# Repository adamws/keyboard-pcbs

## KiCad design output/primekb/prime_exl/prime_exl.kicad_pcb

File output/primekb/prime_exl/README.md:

## primekb/prime_exl

[layout](prime_exl-kle.json) - [PCB](prime_exl.kicad_pcb)

{:loading="lazy"}

[Open in keyboard-layout-editor](http://www.keyboard-layout-editor.com/##@@_x:0.25&y:0.46&c=#aaaaaa;&=4,0&=5,0&=4,1&=5,1&=4,2&=5,2;&@_x:0.25;&=3,0&=6,0&_c=#cccccc;&=3,1&=6,1&=3,2&_c=#aaaaaa;&=6,2;&@_x:0.25;&=2,0&=7,0&_c=#cccccc;&=2,1&=7,1&=2,2&_c=#aaaaaa;&=7,2;&@_x:0.25;&=1,0&=8,0&_c=#cccccc;&=1,1&=8,1&=1,2&_c=#aaaaaa;&=8,2;&@_x:0.25;&=0,0&=9,0&=0,1&_c=#cccccc;&=9,1&=0,2&_c=#aaaaaa;&=9,2;&@_rx:6.25&x:0.85&y:0.46&c=#777777;&=4,3&_c=#cccccc;&=5,3&_x:8.95;&=4,8&_c=#aaaaaa&w:2;&=5,8;&@_x:0.71&y:0.01&w:1.26;&=3,3&_x:-0.01&c=#cccccc;&=6,3&_x:9.23;&=3,8&_c=#777777&w:1.75;&=6,8;&@_x:0.56&y:0.01&c=#aaaaaa&w:1.75;&=2,3&_c=#cccccc;&=7,3&_x:8.52;&=7,7&=2,8&_c=#aaaaaa&w:1.25;&=7,8;&@_x:0.67&y:0.01&w:1.25;&=1,3&_w:1.25;&=8,3&_x:8.8&w:1.5;&=8,7&_w:1.5;&=1,8;&@_r:8&ry:1&x:3.0&y:-1&c=#cccccc;&=4,4&=5,4&=4,5&=5,5;&@_x:3.25;&=3,4&=6,4&=3,5&=6,5;&@_x:3.75;&=2,4&=7,4&=2,5&=7,5;&@_x:3.75&c=#aaaaaa;&=1,4&=8,4&_w:2;&=1,5;&@_r:-8&x:7.5&y:-1.9&c=#cccccc;&=4,6&=5,6&=4,7&=5,7;&@_x:7.75;&=3,6&=6,6&=3,7&=6,7;&@_x:7.25;&=8,5&=2,6&=7,6&=2,7;&@_x:7.25&c=#aaaaaa&w:2;&=1,6&=8,6&=1,7)

{:loading="lazy"}

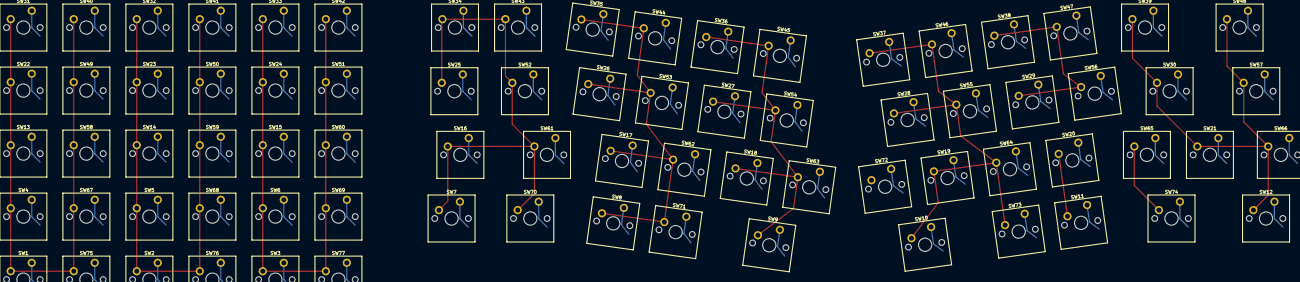
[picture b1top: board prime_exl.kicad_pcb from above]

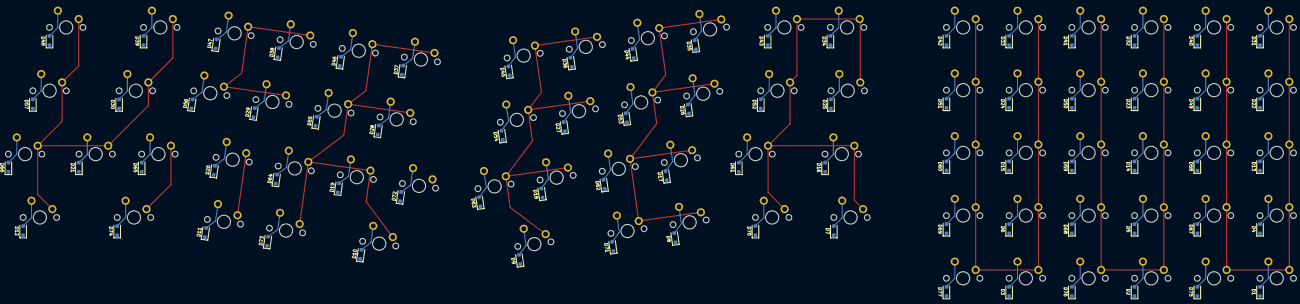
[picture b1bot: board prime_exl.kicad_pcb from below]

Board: 2 copper layers, 154 parts (77 on the bottom side), 96 nets.

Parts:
D1, D2, D3, D4, D5, D6, D7, D8, D9, D10, D11, D12, D13, D14, D15, D16, D17, D18, D19, D20, D21, D22, D23, D24, D25, D26, D27, D28, D29, D30, D31, D32, D33, D34, D35, D36, D37, D38, D39, D40, D41, D42, D43, D44, D45, D46, D47, D48, D49, D50, D51, D52, D53, D54, D55, D56, D57, D58, D59, D60, D61, D62, D63, D64, D65, D66, D67, D68, D69, D70, D71, D72, D73, D74, D75, D76, D77: D_SOD-123F
SW1, SW2, SW3, SW4, SW5, SW6, SW7, SW8, SW9, SW10, SW11, SW12, SW13, SW14, SW15, SW16, SW17, SW18, SW19, SW20, SW21, SW22, SW23, SW24, SW25, SW26, SW27, SW28, SW29, SW30, SW31, SW32, SW33, SW34, SW35, SW36, SW37, SW38, SW39, SW40, SW41, SW42, SW43, SW44, SW45, SW46, SW47, SW48, SW49, SW50, SW51, SW52, SW53, SW54, SW55, SW56, SW57, SW58, SW59, SW60, SW61, SW62, SW63, SW64, SW65, SW66, SW67, SW68, SW69, SW70, SW71, SW72, SW73, SW74, SW75, SW76, SW77: SW_Cherry_MX_PCB_1.00u

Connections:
COL0: SW1.1, SW4.1, SW13.1, SW22.1, SW31.1, SW40.1, SW49.1, SW58.1, SW67.1, SW75.1
COL1: SW2.1, SW5.1, SW14.1, SW23.1, SW32.1, SW41.1, SW50.1, SW59.1, SW68.1, SW76.1
COL2: SW3.1, SW6.1, SW15.1, SW24.1, SW33.1, SW42.1, SW51.1, SW60.1, SW69.1, SW77.1
COL3: SW7.1, SW16.1, SW25.1, SW34.1, SW43.1, SW52.1, SW61.1, SW70.1
COL4: SW8.1, SW17.1, SW26.1, SW35.1, SW44.1, SW53.1, SW62.1, SW71.1
COL5: SW9.1, SW18.1, SW27.1, SW36.1, SW45.1, SW54.1, SW63.1, SW72.1
COL6: SW10.1, SW19.1, SW28.1, SW37.1, SW46.1, SW55.1, SW64.1, SW73.1
COL7: SW11.1, SW20.1, SW29.1, SW38.1, SW47.1, SW56.1, SW65.1, SW74.1
COL8: SW12.1, SW21.1, SW30.1, SW39.1, SW48.1, SW57.1, SW66.1
unnamed: D1.2, SW1.2
unnamed: D2.2, SW2.2
unnamed: D3.2, SW3.2
unnamed: D4.2, SW4.2
unnamed: D5.2, SW5.2
unnamed: D6.2, SW6.2
unnamed: D7.2, SW7.2
unnamed: D8.2, SW8.2
unnamed: D9.2, SW9.2
unnamed: D10.2, SW10.2
unnamed: D11.2, SW11.2
unnamed: D12.2, SW12.2
unnamed: D13.2, SW13.2
unnamed: D14.2, SW14.2
unnamed: D15.2, SW15.2
unnamed: D16.2, SW16.2
unnamed: D17.2, SW17.2
unnamed: D18.2, SW18.2
unnamed: D19.2, SW19.2
unnamed: D20.2, SW20.2
unnamed: D21.2, SW21.2
unnamed: D22.2, SW22.2
unnamed: D23.2, SW23.2
unnamed: D24.2, SW24.2
unnamed: D25.2, SW25.2
unnamed: D26.2, SW26.2
unnamed: D27.2, SW27.2
unnamed: D28.2, SW28.2
unnamed: D29.2, SW29.2
unnamed: D30.2, SW30.2
unnamed: D31.2, SW31.2
unnamed: D32.2, SW32.2
unnamed: D33.2, SW33.2
unnamed: D34.2, SW34.2
unnamed: D35.2, SW35.2
unnamed: D36.2, SW36.2
unnamed: D37.2, SW37.2
unnamed: D38.2, SW38.2
unnamed: D39.2, SW39.2
unnamed: D40.2, SW40.2
unnamed: D41.2, SW41.2
unnamed: D42.2, SW42.2
unnamed: D43.2, SW43.2
unnamed: D44.2, SW44.2
unnamed: D45.2, SW45.2
unnamed: D46.2, SW46.2
unnamed: D47.2, SW47.2
unnamed: D48.2, SW48.2
unnamed: D49.2, SW49.2
unnamed: D50.2, SW50.2
unnamed: D51.2, SW51.2
unnamed: D52.2, SW52.2
unnamed: D53.2, SW53.2
unnamed: D54.2, SW54.2
unnamed: D55.2, SW55.2
unnamed: D56.2, SW56.2
unnamed: D57.2, SW57.2
unnamed: D58.2, SW58.2
unnamed: D59.2, SW59.2
unnamed: D60.2, SW60.2
unnamed: D61.2, SW61.2
unnamed: D62.2, SW62.2
unnamed: D63.2, SW63.2
unnamed: D64.2, SW64.2
unnamed: D65.2, SW65.2
unnamed: D66.2, SW66.2
unnamed: D67.2, SW67.2
unnamed: D68.2, SW68.2
unnamed: D69.2, SW69.2
unnamed: D70.2, SW70.2
unnamed: D71.2, SW71.2
unnamed: D72.2, SW72.2
unnamed: D73.2, SW73.2
unnamed: D74.2, SW74.2
unnamed: D75.2, SW75.2
unnamed: D76.2, SW76.2
unnamed: D77.2, SW77.2
ROW0: D1.1, D2.1, D3.1
ROW1: D4.1, D5.1, D6.1, D7.1, D8.1, D9.1, D10.1, D11.1, D12.1
ROW2: D13.1, D14.1, D15.1, D16.1, D17.1, D18.1, D19.1, D20.1, D21.1
ROW3: D22.1, D23.1, D24.1, D25.1, D26.1, D27.1, D28.1, D29.1, D30.1
ROW4: D31.1, D32.1, D33.1, D34.1, D35.1, D36.1, D37.1, D38.1, D39.1
ROW5: D40.1, D41.1, D42.1, D43.1, D44.1, D45.1, D46.1, D47.1, D48.1
ROW6: D49.1, D50.1, D51.1, D52.1, D53.1, D54.1, D55.1, D56.1, D57.1
ROW7: D58.1, D59.1, D60.1, D61.1, D62.1, D63.1, D64.1, D65.1, D66.1
ROW8: D67.1, D68.1, D69.1, D70.1, D71.1, D72.1, D73.1, D74.1
ROW9: D75.1, D76.1, D77.1
